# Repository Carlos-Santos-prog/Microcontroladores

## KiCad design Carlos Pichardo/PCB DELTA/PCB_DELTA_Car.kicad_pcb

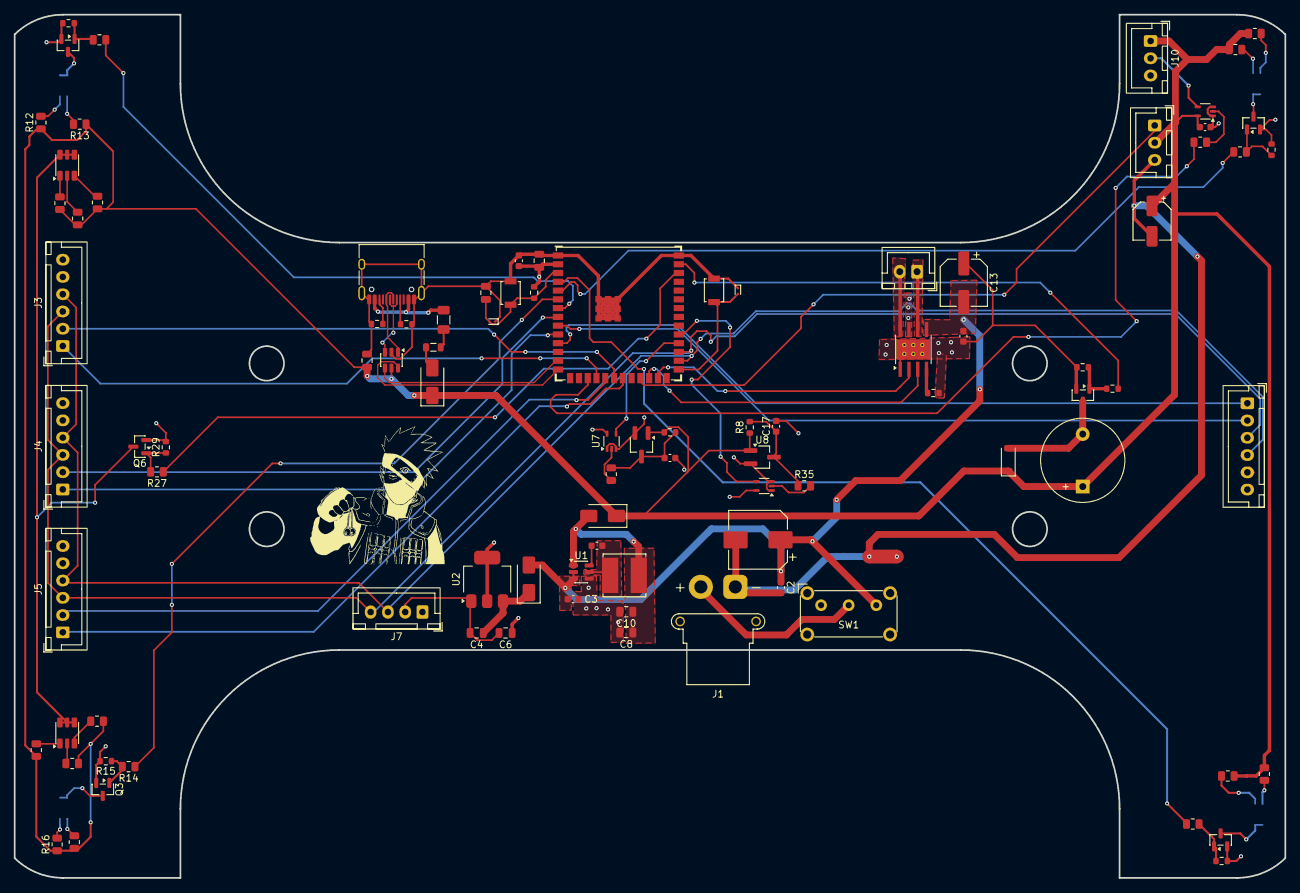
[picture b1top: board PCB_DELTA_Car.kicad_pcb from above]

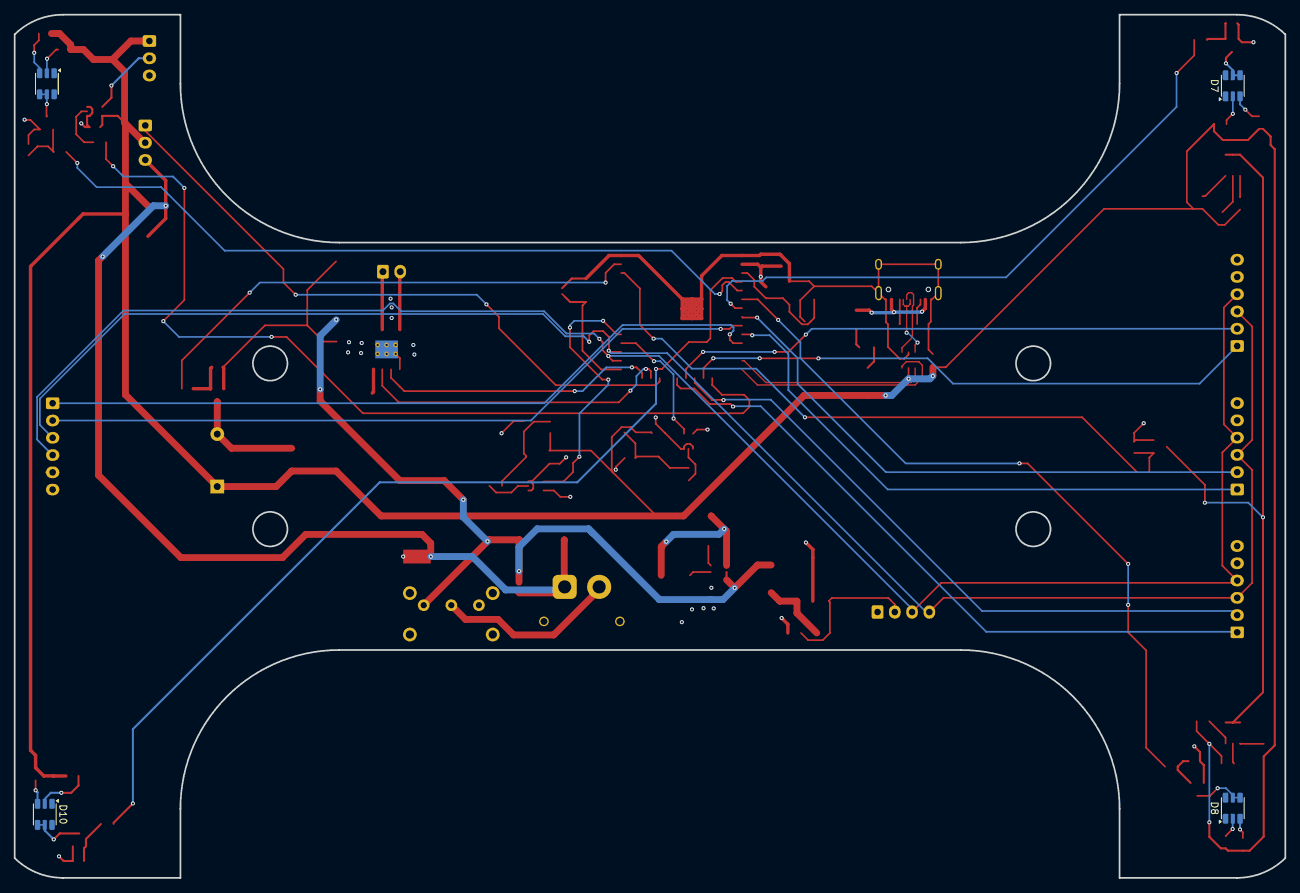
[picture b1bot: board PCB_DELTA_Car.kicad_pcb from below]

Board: 4 copper layers, 184.0 x 125.0 mm, 99 parts (4 on the bottom side), 78 nets.

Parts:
BZ1: Buzzer; Buzzer_12x9.5RM7.6
C1: 470uF; CP_Elec_8x10
C2, C5, C9: 100nF; C_0603_1608Metric
C3: 10uF; C_0603_1608Metric
C4: 10uF; C_0805_2012Metric
C6, C7, C8, C10: 22uF; C_0805_2012Metric
C11: 47uF; CP_Elec_5x4.5
C12, C16, C17, C18: 0.1uF; C_0603_1608Metric
C13: 47uF; CP_Elec_6.3x5.4
C14: 100nF; C_0805_2012Metric
C15: 1uf; C_0805_2012Metric
D1, D2, D4: D_Schottky; D_SMA
D3: 1N4148W; D_SOD-123
D5, D6: ESD3.3; D_SOD-923
D7, D8, D9, D10, D11, D12: SMLVN6RGB; LED_ROHM_SMLVN6
F1: Polyfuse 1A; Fuse_1206_3216Metric
FB1: FerriteBead; L_0805_2012Metric
J1: Conn_batt; AMASS_XT30PW-F_1x02_P2.50mm_Horizontal
J2: Servo; JST_XH_B3B-XH-A_1x03_P2.50mm_Vertical
J3, J4, J5, J6: Conn_01x06_Pin; JST_XH_B6B-XH-A_1x06_P2.50mm_Vertical
J7: Sens_Temp; JST_XH_B4B-XH-A_1x04_P2.50mm_Vertical
J8: Conn_01x02_Socket; JST_XH_B2B-XH-A_1x02_P2.50mm_Vertical
J9: USB_C_Receptacle_USB2.0_16P; USB_C_Receptacle_HRO_TYPE-C-31-M-12
J10: Conn_01x03_Pin; JST_XH_B3B-XH-A_1x03_P2.50mm_Vertical
L1: 4.7uH; L_Bourns_SRN6045TA
NT1: NetTie_2; NetTie-2_SMD_Pad2.0mm
Q1: MMBT2222A; SOT-23
Q2, Q3, Q4, Q5, Q6: 2N7002H; SOT-23
R1: 1k; R_0603_1608Metric
R2, R11, R15, R19, R23, R29: 10k; R_0603_1608Metric
R3: 30K; R_0603_1608Metric
R4: 5.1kΩ; R_0603_1608Metric
R5: 5.1 kΩ; R_0603_1608Metric
R6: 10K; R_0603_1608Metric
R7, R8: 5.1k; R_0603_1608Metric
R9, R10, R14, R18, R22, R27, R34, R35: 30; R_0805_2012Metric
R12, R16, R20, R24, R26, R30, R31, R33: 100; R_0805_2012Metric
R13, R17, R21, R25, R28, R32: 150; R_0805_2012Metric
SW1: SW_SPDT; SW_E-Switch_EG1224_SPDT_Angled
SW2: BOOT; SW_SPST_B3U-1000P
SW3: RESET; SW_SPST_B3U-1000P
U1: AP63205WU; TSOT-23-6
U2: LD1117S33TR_SOT223; SOT-223-3_TabPin2
U3: DRV8871DDA; Texas_HTSOP-8-1EP_3.9x4.9mm_P1.27mm_EP2.95x4.9mm_Mask2.4x3.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
U4: USBLC6-2SC6; SOT-23-6
U5: ESP32-S3-WROOM-1; ESP32-S3-WROOM-1U
U6, U8: A1101xUA; SOT-23W_Handsoldering
U7, U9, U10: SN74LVC1G125DCK; Texas_R-PDSO-G5_DCK-5

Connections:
+3V3: C6.1, C7.1, C9.1, J3.6, J4.6, J5.6, J6.6, J7.1, R6.1, U2.2 (VO), U5.2 (3V3), U7.5 (VCC), U9.5 (VCC)
+5V: BZ1.1 (+), C11.1, C14.2, C18.1, D2.1 (K), D3.1 (K), D4.1 (K), J2.2, J10.1, R7.1, R8.1, R12.1, R13.1, R16.1, R17.1, R20.1, R21.1, R24.1, R25.1, R26.1, R28.1, R30.1, R31.1, R32.1, R33.1, U4.5 (VBUS), U6.1 (V_{CC}), U8.1 (V_{CC}), U10.5 (VCC)
+BATT: C1.1, C2.1, C3.1, C12.2, C13.2, D1.2 (A), SW1.3 (C), U1.2 (EN), U1.3 (IN), U3.5 (VM)
/Buzzer/Buzzer: R1.1, U5.39 (GPIO1/TOUCH1/ADC1_CH0)
/ESP32_S3/D+: U4.6 (I/O1), U5.14 (GPIO20/U1CTS/ADC2_CH9/CLK_OUT1/USB_D+)
/ESP32_S3/D-: U4.4 (I/O2), U5.13 (GPIO19/U1RTS/ADC2_CH8/CLK_OUT2/USB_D-)
/ESP32_S3/EN: C15.2, D6.2 (A2), R6.2, SW3.2 (B), U5.3 (EN)
/ESP32_S3/GPIO0: D5.2 (A2), SW2.2 (B), U5.27 (GPIO0/BOOT)
/ESP32_S3/GPIO2: R27.1, U5.38 (GPIO2/TOUCH2/ADC1_CH1)
/ESP32_S3/GPIO4: R22.1, U5.4 (GPIO4/TOUCH4/ADC1_CH3)
/ESP32_S3/GPIO5: R18.1, U5.5 (GPIO5/TOUCH5/ADC1_CH4)
/ESP32_S3/GPIO6: R14.1, U5.6 (GPIO6/TOUCH6/ADC1_CH5)
/ESP32_S3/GPIO7: R10.1, U5.7 (GPIO7/TOUCH7/ADC1_CH6)
/ESP32_S3/GPIO9: R9.1, U5.17 (GPIO9/TOUCH9/ADC1_CH8/FSPIHD/SUBSPIHD)
/ESP32_S3/GPIO10: J3.1, U5.18 (GPIO10/TOUCH10/ADC1_CH9/FSPICS0/FSPIIO4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)
/ESP32_S3/GPIO11: J5.2, U5.19 (GPIO11/TOUCH11/ADC2_CH0/FSPID/FSPIIO5/S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)
/ESP32_S3/GPIO12: J3.2, U5.20 (GPIO12/TOUCH12/ADC2_CH1/FSPICLK/FSPIIO6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)
/ESP32_S3/GPIO13: J5.1, U5.21 (GPIO13/TOUCH13/ADC2_CH2/FSPIQ/FSPIIO7/S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)
/ESP32_S3/GPIO15: J4.2, U5.8 (GPIO15/U0RTS/ADC2_CH4/XTAL_32K_P)
/ESP32_S3/GPIO16: J6.2, U5.9 (GPIO16/U0CTS/ADC2_CH5/XTAL_32K_N)
/ESP32_S3/GPIO17: J4.1, U5.10 (GPIO17/U1TXD/ADC2_CH6)
/ESP32_S3/GPIO18: J6.1, U5.11 (GPIO18/U1RXD/ADC2_CH7/CLK_OUT3)
/ESP32_S3/GPIO21: J2.1, U5.23 (GPIO21)
/ESP32_S3/GPIO37: U5.30 (SPIDQS/GPIO37/FSPIQ/SUBSPIQ), U7.4
/ESP32_S3/GPIO38: U5.31 (GPIO38/FSPIWP/SUBSPIWP), U9.4
/ESP32_S3/GPIO47: U3.3 (IN1), U5.24 (GPIO47/SPICLK_P/SUBSPICLK_P_DIFF)
/ESP32_S3/GPIO48: U3.2 (IN2), U5.25 (GPIO48/SPICLK_N/SUBSPICLK_N_DIFF)
/SCL: J3.3, J4.3, J5.3, J6.3, J7.4, U5.29 (SPIIO7/GPIO36/FSPICLK/SUBSPICLK)
/SDA: J3.4, J4.4, J5.4, J6.4, J7.3, U5.28 (SPIIO6/GPIO35/FSPID/SUBSPID)
/USB_C/USB_D+: J9.A6 (D+), J9.B6 (D+), U4.1 (I/O1)
/USB_C/USB_D-: J9.A7 (D-), J9.B7 (D-), U4.3 (I/O2)
GND: C3.2, C4.2, C6.2, C7.2, C8.2, C9.2, C10.2, C12.1, C13.1, C14.1, C15.1, C16.2, C17.2, C18.2, D5.1 (A1), D6.1 (A1), J3.5, J4.5, J5.5, J6.5, J7.2, J9.A1 (GND), J9.A12 (GND), J9.B1 (GND), J9.B12 (GND), J9.SH (SHIELD), J10.3, NT1.2, Q1.2 (E), Q2.2 (S), Q3.2 (S), Q4.2 (S), Q5.2 (S), Q6.2 (S), R2.1, R3.2, R4.2, R5.2, R11.2, R15.2, R19.2, R23.2, R29.2, SW2.1 (A), SW3.1 (A), U1.4 (GND), U2.1 (GND), U3.1 (GND), U3.7 (GND), U3.9 (GND), U4.2 (GND), U5.1 (GND), U5.40 (GND), U5.41 (GND), U6.2 (GND), U7.1, U7.3 (GND), U8.2 (GND), U9.1, U9.3 (GND), U10.1, U10.3 (GND)
GNDPWR: C1.2, C2.2, C11.2, J1.1, J2.3, NT1.1
unnamed: BZ1.2 (-), D3.2 (A), Q1.3 (C)
unnamed: C8.1, C10.1, D2.2 (A), L1.2, U1.1 (FB)
unnamed: D4.2 (A), FB1.1
unnamed: D7.3 (GA), R12.2
unnamed: D7.4 (GK), D7.5 (RK), Q2.3 (D)
unnamed: D7.2 (RA), R13.2
unnamed: D8.3 (GA), R16.2
unnamed: D8.4 (GK), D8.5 (RK), Q3.3 (D)
unnamed: D8.2 (RA), R17.2
unnamed: D9.3 (GA), R20.2
unnamed: D9.4 (GK), D9.5 (RK), Q4.3 (D)
unnamed: D9.2 (RA), R21.2
unnamed: D10.3 (GA), R24.2
unnamed: D10.4 (GK), D10.5 (RK), Q5.3 (D)
unnamed: D10.2 (RA), R25.2
unnamed: D11.1 (BA), R30.2
unnamed: D11.4 (GK), D11.5 (RK), D11.6 (BK), D12.4 (GK), D12.5 (RK), D12.6 (BK), Q6.3 (D)
unnamed: D11.3 (GA), R26.2
unnamed: D11.2 (RA), R28.2
unnamed: D12.1 (BA), R33.2
unnamed: D12.3 (GA), R31.2
unnamed: D12.2 (RA), R32.2
unnamed: F1.1, J9.A4 (VBUS), J9.A9 (VBUS), J9.B4 (VBUS), J9.B9 (VBUS)
unnamed: F1.2, FB1.2
unnamed: J1.2, SW1.2 (B)
unnamed: J8.1, U3.6 (OUT1)
unnamed: J8.2, U3.8 (OUT2)
unnamed: J9.A5 (CC1), R5.1
unnamed: J9.B5 (CC2), R4.1
unnamed: J10.2, U10.4
unnamed: Q1.1 (B), R1.2, R2.2
unnamed: Q2.1 (G), R10.2, R11.1
unnamed: Q3.1 (G), R14.2, R15.1
unnamed: Q4.1 (G), R18.2, R19.1
unnamed: Q5.1 (G), R22.2, R23.1
unnamed: Q6.1 (G), R27.2, R29.1
unnamed: R9.2, U10.2
unnamed: R34.2, U7.2
unnamed: R35.2, U9.2
unnamed: C5.2, U1.6 (BST)
unnamed: C5.1, L1.1, U1.5 (SW)
unnamed: R3.1, U3.4 (ILIM)
unnamed: C16.1, R7.2, R34.1, U6.3 (V_{OUT})
unnamed: C17.1, R8.2, R35.1, U8.3 (V_{OUT})
VBUS: C4.1, D1.1 (K), U2.3 (VI)
